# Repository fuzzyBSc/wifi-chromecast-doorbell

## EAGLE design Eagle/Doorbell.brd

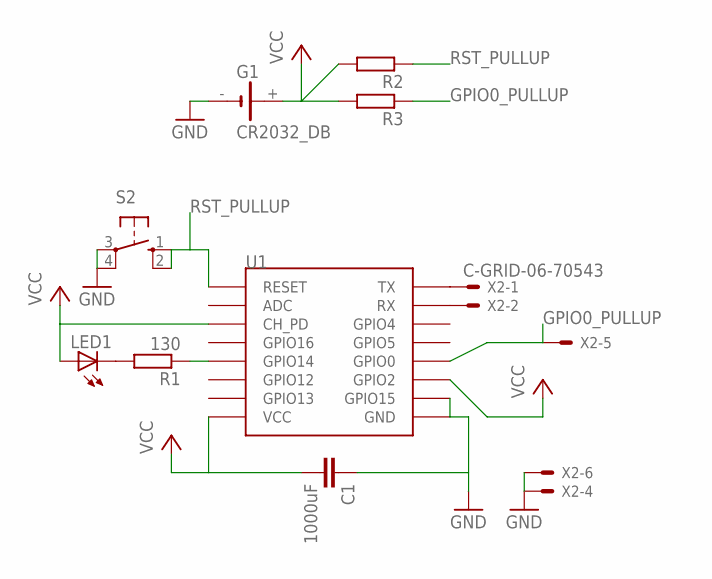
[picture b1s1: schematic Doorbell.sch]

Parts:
C1: 1000uF; C5B3.5
G1: CR2032_DB; CR2032_DOORBELL
LED1: LED3MM
R1: 130; 0204/5
R2, R3: R-EU_0204/5; 0204/5
S2: 10-XX; B3F-10XX
U1: ESP12
X2: C-GRID-06-70543; 70543-06

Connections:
GND: C1.1, G1.-, S2.3, S2.4 (P1), U1.GND, U1.GPIO15, X2.4, X2.6
GPIO0_PULLUP: R3.1, U1.GPIO0, X2.5
unnamed: U1.TX, X2.1
unnamed: U1.RX, X2.2
unnamed: R1.1, U1.GPIO14
unnamed: LED1.K (C), R1.2
RST_PULLUP: R2.1, S2.1 (S), S2.2 (S1), U1.RESET
VCC: C1.2, G1.+, LED1.A, R2.2, R3.2, U1.CH_PD, U1.GPIO2, U1.VCC

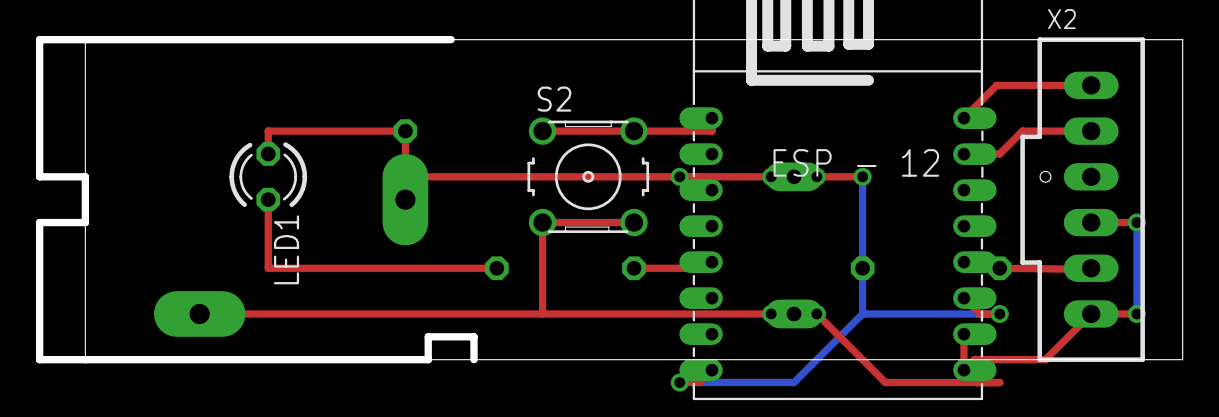
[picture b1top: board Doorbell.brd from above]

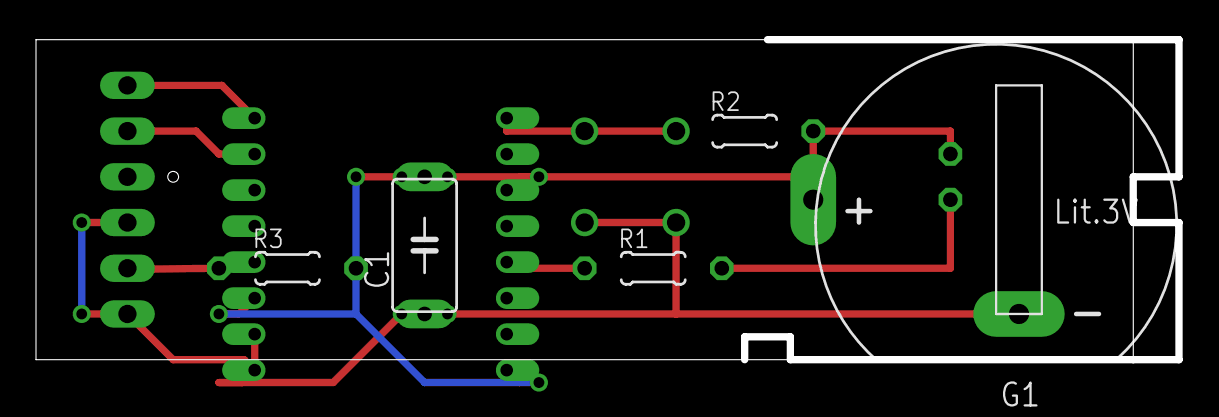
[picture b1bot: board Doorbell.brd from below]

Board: 2 copper layers, 63.3 x 17.8 mm, 9 parts (5 on the bottom side), 8 nets.

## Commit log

2017-01-05 Add python script to connect and ring the bell
2017-01-06 Support default/all devices
2017-01-09 mod_python integration
2017-04-13 Initial eagle checkin
